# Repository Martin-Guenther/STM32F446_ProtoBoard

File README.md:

# STM32F446_ProtoBoard

A minimalist board with an STM32F446 microcontroller that can be used for prototypes. Most pins of the chip are routed to headers. It is powered over a USB connector and can also act as a USB device. It has SPI flash memory included and must be programmed via SWD.

### License
This is Open-Source-Hardware released under the GNU GPL license.

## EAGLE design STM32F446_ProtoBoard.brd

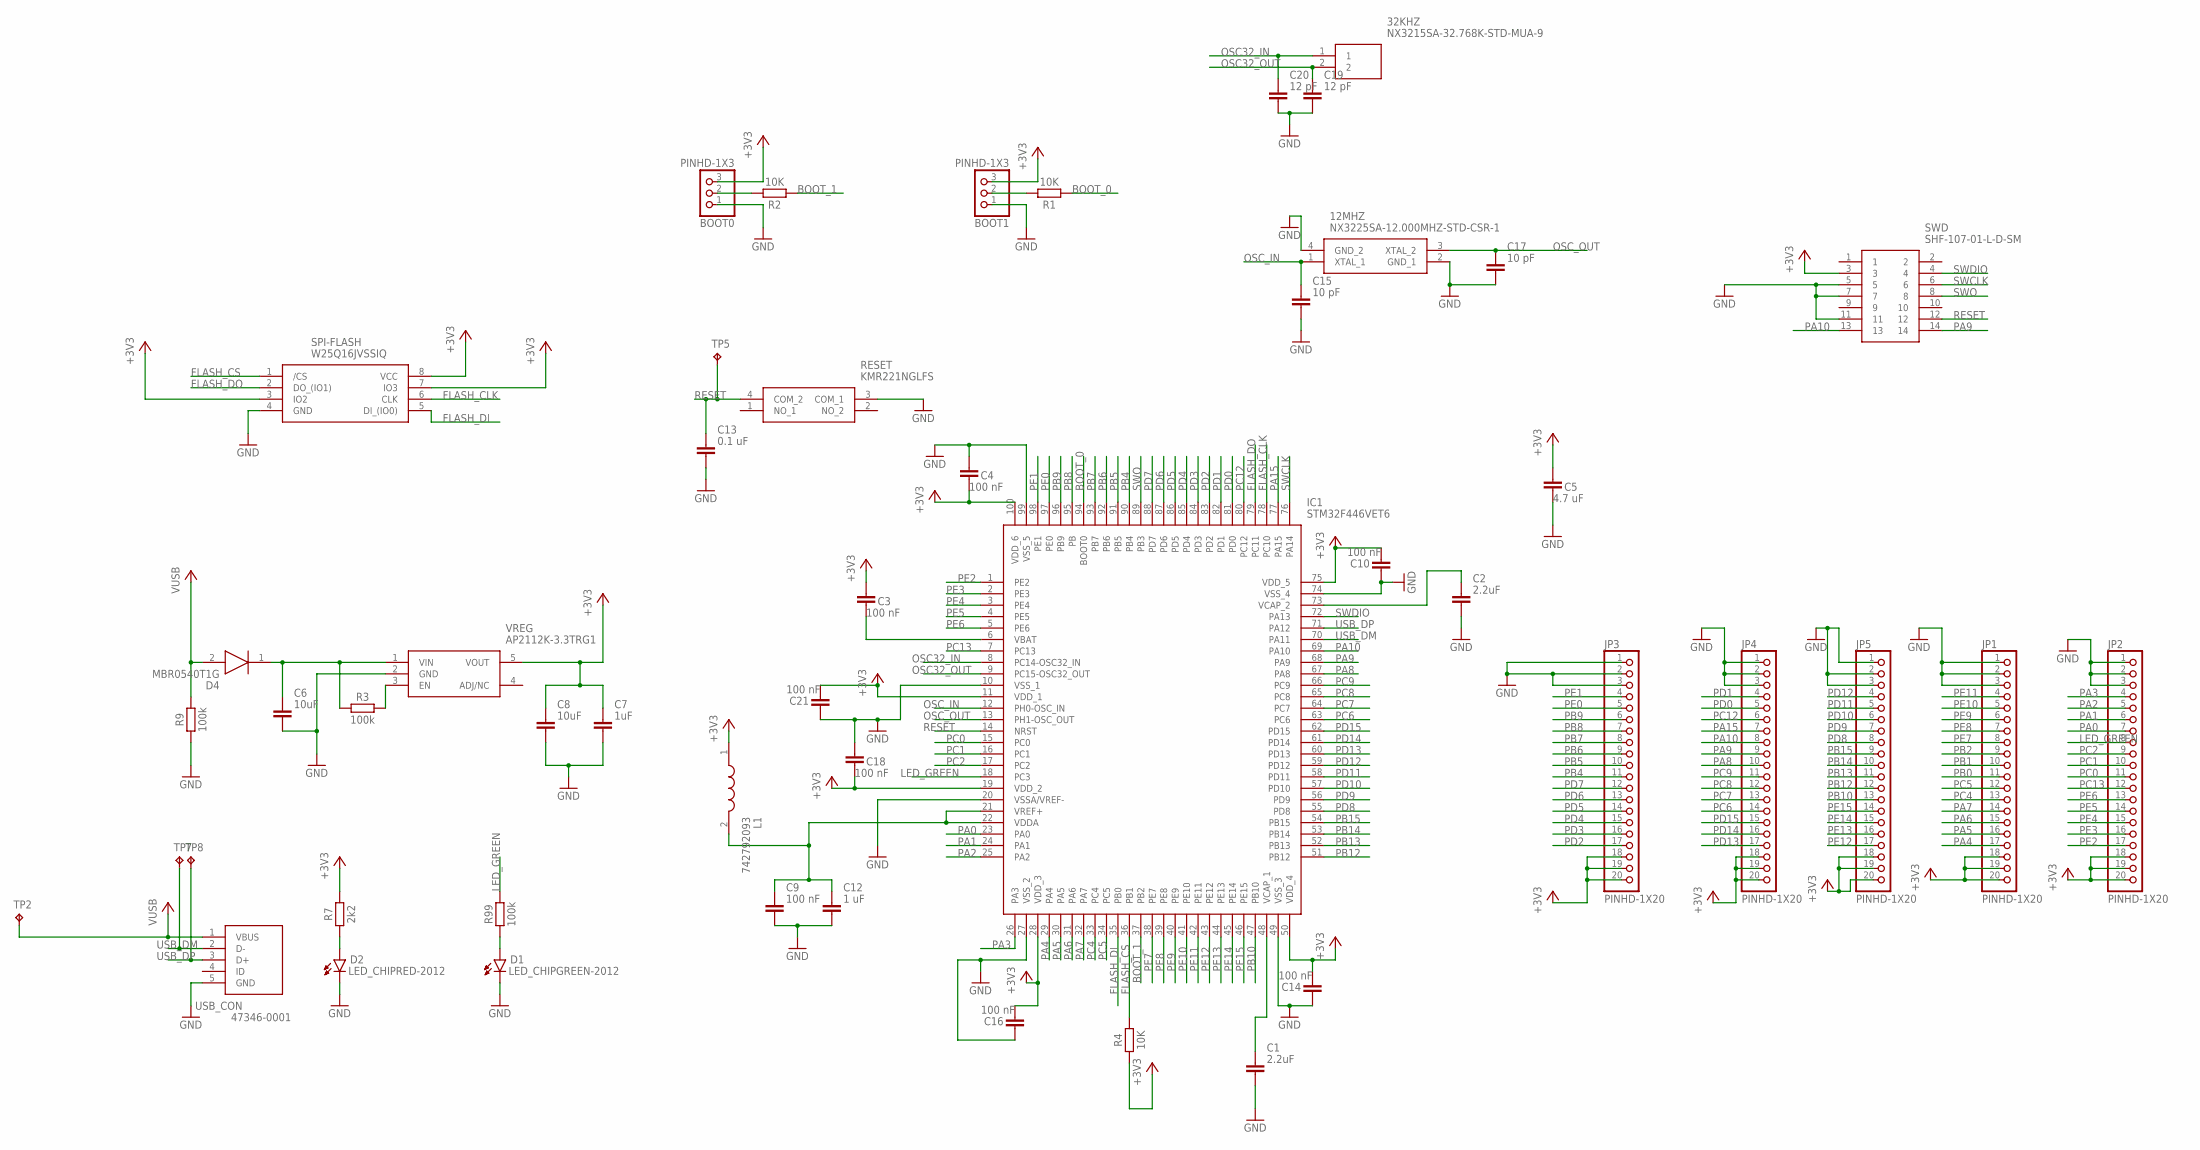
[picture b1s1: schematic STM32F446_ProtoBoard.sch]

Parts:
12MHZ: NX3225SA-12.000MHZ-STD-CSR-1; NX3225SA12000MHZSTDCSR1
32KHZ: NX3215SA-32.768K-STD-MUA-9; NX3215SA
BOOT0, BOOT1: PINHD-1X3; 1X03
C1, C2: 2.2uF; CAPC2012X110
C3, C4, C9, C10, C14, C16, C18, C21: 100 nF; CAPC2012X110
C5: 4.7 uF; CAPC2012X110
C6, C8: 10uF; CAPC2012X110
C7: 1uF; CAPC2012X110
C12: 1 uF; CAPC2012X110
C13: 0.1 uF; CAPC2012X110
C15, C17: 10 pF; CAPC2012X110
C19, C20: 12 pF; CAPC2012X110
D1: LED_CHIPGREEN-2012; LEDC2012X110N_G
D2: LED_CHIPRED-2012; LEDC2012X110N_R
D4: MBR0540T1G; SOD3716X135N
IC1: STM32F446VET6; QFP50P1600X1600X160-100N
JP1, JP2, JP3, JP4, JP5: PINHD-1X20; 1X20
L1: 742792093; CAPC2012X110N
R1, R2, R4: 10K; RESC2012X65
R3, R9, R99: 100k; RESC2012X65
R7: 2k2; RESC2012X65
RESET: KMR221NGLFS
SPI-FLASH: W25Q16JVSSIQ; SOIC127P790X216-8N
SWD: SHF-107-01-L-D-SM; SHF-107-01-X-D-SM
TP2, TP5, TP7, TP8: TPTP20R; TP20R
USB_CON: 47346-0001
VREG: AP2112K-3.3TRG1; SOT95P282X130-5N

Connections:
+3V3: BOOT0.3, BOOT1.3, C3.1, C4.2, C5.1, C7.1, C8.1, C10.2, C14.2, C16.2, C18.2, C21.2, IC1.11 (VDD_1), IC1.19 (VDD_2), IC1.28 (VDD_3), IC1.50 (VDD_4), IC1.75 (VDD_5), IC1.100 (VDD_6), JP1.18, JP1.19, JP1.20, JP2.18, JP2.19, JP2.20, JP3.18, JP3.19, JP3.20, JP4.18, JP4.19, JP4.20, JP5.18, JP5.19, JP5.20, L1.1, R4.1, R7.2, SPI-FLASH.3 (IO2), SPI-FLASH.7 (IO3), SPI-FLASH.8 (VCC), SWD.3, VREG.5 (VOUT)
+5V: D4.2 (A), R9.2, TP2.TP, USB_CON.1 (VBUS)
BOOT_0: IC1.94 (BOOT0), R1.1
BOOT_1: IC1.37 (PB2), R2.1
FLASH_CLK: IC1.78 (PC10), SPI-FLASH.6 (CLK)
FLASH_CS: IC1.36 (PB1), R4.2, SPI-FLASH.1 (/CS)
FLASH_DI: IC1.35 (PB0), SPI-FLASH.5 (DI_(IO0))
FLASH_DO: IC1.79 (PC11), SPI-FLASH.2 (DO_(IO1))
GND: 12MHZ.2 (GND_1), 12MHZ.4 (GND_2), BOOT0.1, BOOT1.1, C1.2, C2.2, C4.1, C5.2, C6.2, C7.2, C8.2, C9.2, C10.1, C12.2, C13.2, C14.1, C15.2, C16.1, C17.2, C18.1, C19.2, C20.2, C21.1, D1.1 (C), D2.1 (C), IC1.10 (VSS_1), IC1.20 (VSSA/VREF-), IC1.27 (VSS_2), IC1.49 (VSS_3), IC1.74 (VSS_4), IC1.99 (VSS_5), JP1.1, JP1.2, JP1.3, JP2.1, JP2.2, JP2.3, JP3.1, JP3.2, JP3.3, JP4.1, JP4.2, JP4.3, JP5.1, JP5.2, JP5.3, R9.1, RESET.3 (COM_1), SPI-FLASH.4 (GND), SWD.5, SWD.7, SWD.11, USB_CON.5 (GND), VREG.2 (GND)
LED_GREEN: IC1.18 (PC3), JP2.8, R99.2
unnamed: C6.1, D4.1 (K), R3.1, VREG.1 (VIN)
unnamed: R3.2, VREG.3 (EN)
unnamed: D2.2 (A), R7.1
unnamed: D1.2 (A), R99.1
unnamed: C1.1, IC1.48 (VCAP_1)
unnamed: C3.2, IC1.6 (VBAT)
unnamed: BOOT1.2, R1.2
unnamed: C2.1, IC1.73 (VCAP_2)
unnamed: BOOT0.2, R2.2
unnamed: C9.1, C12.1, IC1.21 (VREF+), IC1.22 (VDDA), L1.2
OSC32_IN: 32KHZ.1, C20.1, IC1.8 (PC14-OSC32_IN)
OSC32_OUT: 32KHZ.2, C19.1, IC1.9 (PC15-OSC32_OUT)
OSC_IN: 12MHZ.1 (XTAL_1), C15.1, IC1.12 (PH0-OSC_IN)
OSC_OUT: 12MHZ.3 (XTAL_2), C17.1, IC1.13 (PH1-OSC_OUT)
PA0: IC1.23 (PA0), JP2.7
PA1: IC1.24 (PA1), JP2.6
PA2: IC1.25 (PA2), JP2.5
PA3: IC1.26 (PA3), JP2.4
PA4: IC1.29 (PA4), JP1.17
PA5: IC1.30 (PA5), JP1.16
PA6: IC1.31 (PA6), JP1.15
PA7: IC1.32 (PA7), JP1.14
PA8: IC1.67 (PA8), JP4.10
PA9: IC1.68 (PA9), JP4.9, SWD.14
PA10: IC1.69 (PA10), JP4.8, SWD.13
PA15: IC1.77 (PA15), JP4.7
PB0: JP1.11
PB1: JP1.10
PB2: JP1.9
PB4: IC1.90 (PB4), JP3.11
PB5: IC1.91 (PB5), JP3.10
PB6: IC1.92 (PB6), JP3.9
PB7: IC1.93 (PB7), JP3.8
PB8: IC1.95 (PB), JP3.7
PB9: IC1.96 (PB9), JP3.6
PB10: IC1.47 (PB10), JP5.13
PB12: IC1.51 (PB12), JP5.12
PB13: IC1.52 (PB13), JP5.11
PB14: IC1.53 (PB14), JP5.10
PB15: IC1.54 (PB15), JP5.9
PC0: IC1.15 (PC0), JP2.11
PC1: IC1.16 (PC1), JP2.10
PC2: IC1.17 (PC2), JP2.9
PC4: IC1.33 (PC4), JP1.13
PC5: IC1.34 (PC5), JP1.12
PC6: IC1.63 (PC6), JP4.14
PC7: IC1.64 (PC7), JP4.13
PC8: IC1.65 (PC8), JP4.12
PC9: IC1.66 (PC9), JP4.11
PC12: IC1.80 (PC12), JP4.6
PC13: IC1.7 (PC13), JP2.12
PD0: IC1.81 (PD0), JP4.5
PD1: IC1.82 (PD1), JP4.4
PD2: IC1.83 (PD2), JP3.17
PD3: IC1.84 (PD3), JP3.16
PD4: IC1.85 (PD4), JP3.15
PD5: IC1.86 (PD5), JP3.14
PD6: IC1.87 (PD6), JP3.13
PD7: IC1.88 (PD7), JP3.12
PD8: IC1.55 (PD8), JP5.8
PD9: IC1.56 (PD9), JP5.7
PD10: IC1.57 (PD10), JP5.6
PD11: IC1.58 (PD11), JP5.5
PD12: IC1.59 (PD12), JP5.4
PD13: IC1.60 (PD13), JP4.17
PD14: IC1.61 (PD14), JP4.16
PD15: IC1.62 (PD15), JP4.15
PE0: IC1.97 (PE0), JP3.5
PE1: IC1.98 (PE1), JP3.4
PE2: IC1.1 (PE2), JP2.17
PE3: IC1.2 (PE3), JP2.16
PE4: IC1.3 (PE4), JP2.15
PE5: IC1.4 (PE5), JP2.14
PE6: IC1.5 (PE6), JP2.13
PE7: IC1.38 (PE7), JP1.8
PE8: IC1.39 (PE8), JP1.7
PE9: IC1.40 (PE9), JP1.6
PE10: IC1.41 (PE10), JP1.5
PE11: IC1.42 (PE11), JP1.4
PE12: IC1.43 (PE12), JP5.17
PE13: IC1.44 (PE13), JP5.16
PE14: IC1.45 (PE14), JP5.15
PE15: IC1.46 (PE15), JP5.14
RESET: C13.1, IC1.14 (NRST), RESET.4 (COM_2), SWD.12, TP5.TP
SWCLK: IC1.76 (PA14), SWD.6
SWDIO: IC1.72 (PA13), SWD.4
SWO: IC1.89 (PB3), SWD.8
USB_DM: IC1.70 (PA11), TP7.TP, USB_CON.2 (D-)
USB_DP: IC1.71 (PA12), TP8.TP, USB_CON.3 (D+)

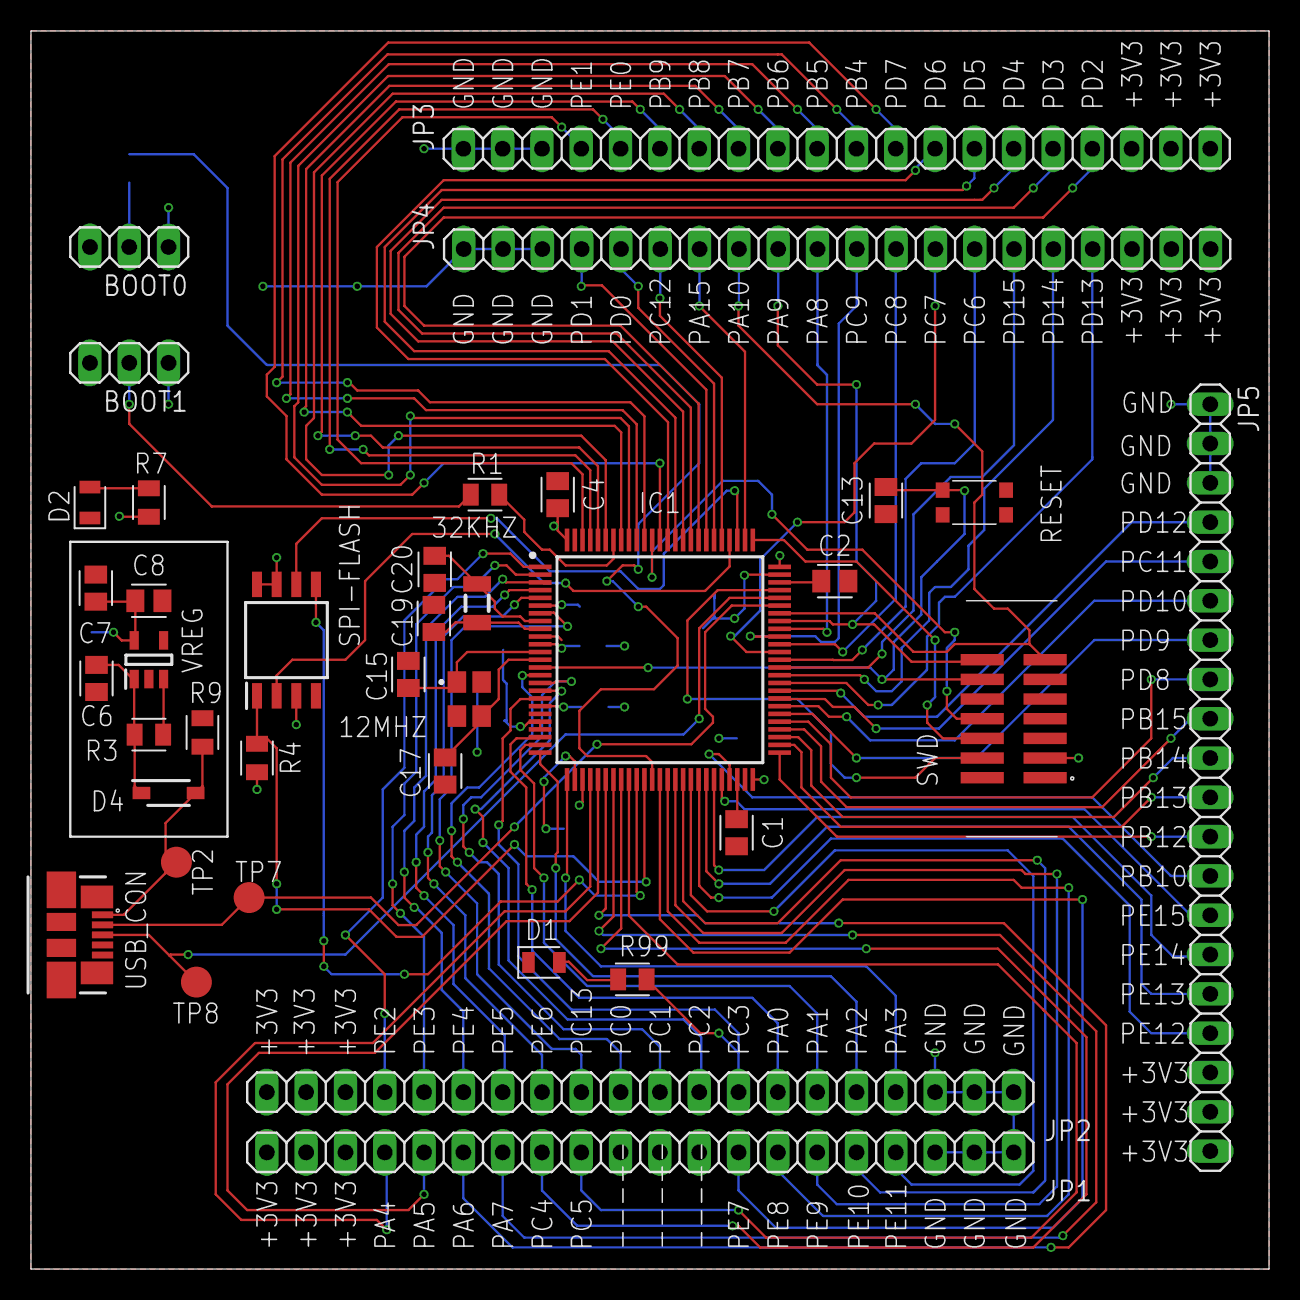
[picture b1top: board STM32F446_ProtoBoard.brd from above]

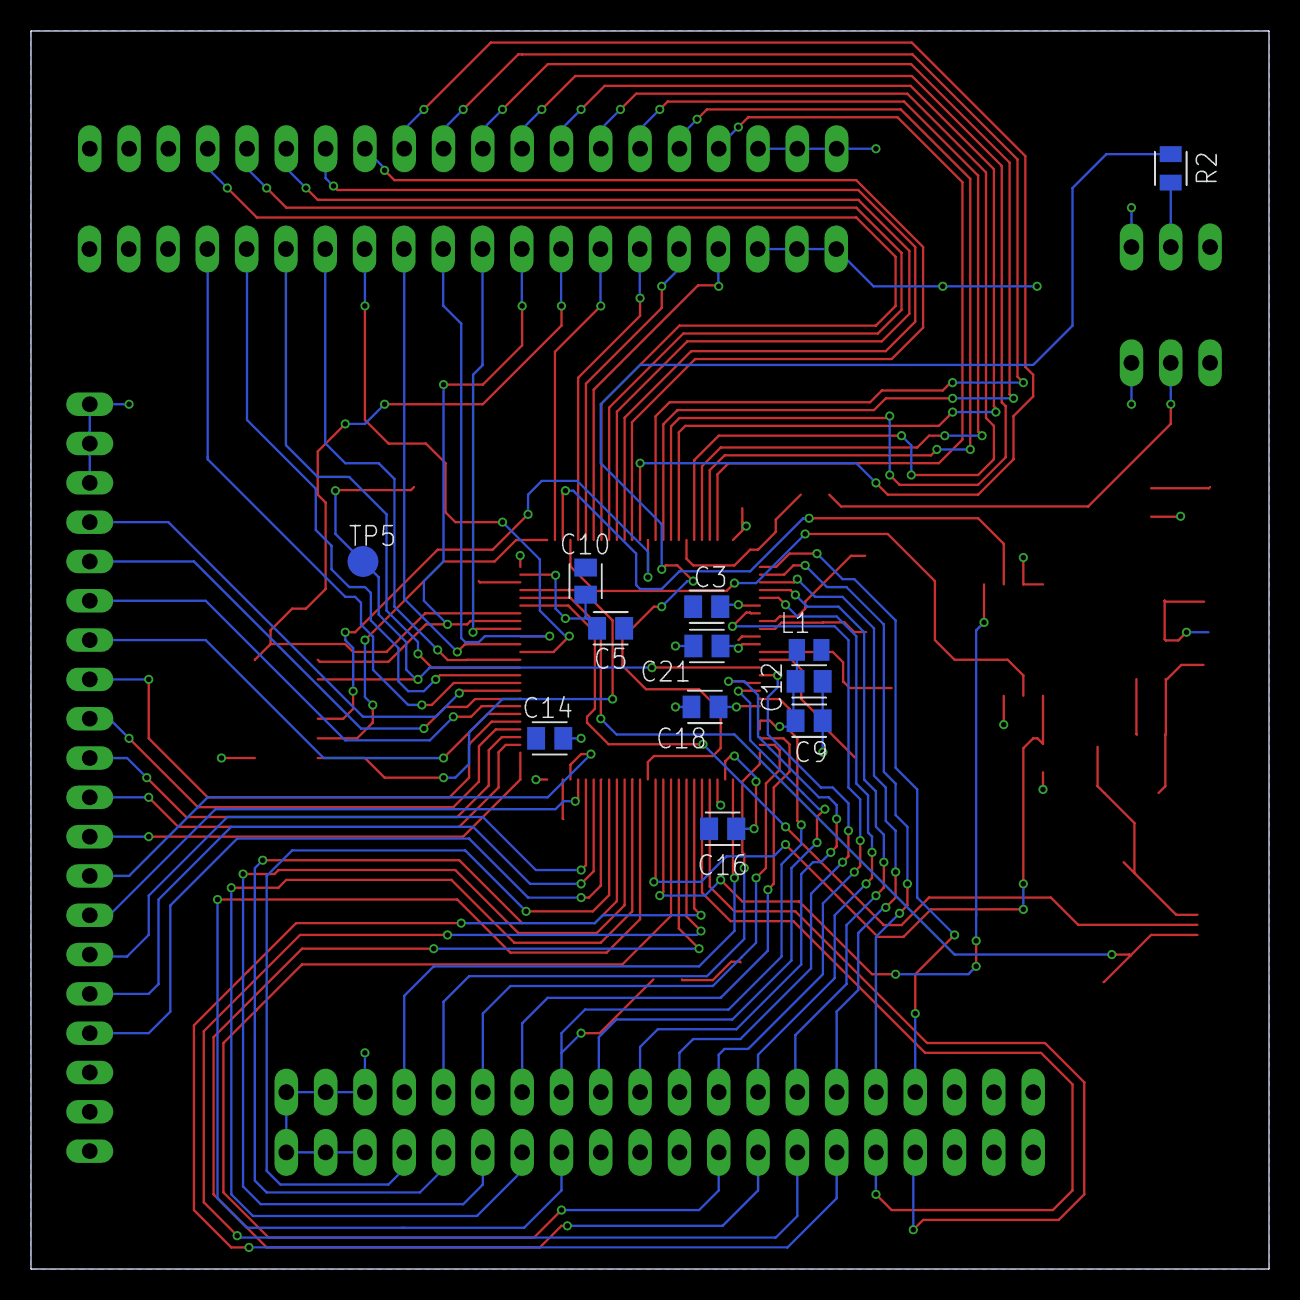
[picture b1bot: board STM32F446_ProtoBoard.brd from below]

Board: 2 copper layers, 80.0 x 80.0 mm, 50 parts (12 on the bottom side), 96 nets.

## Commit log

2020-08-30 Add Eagle files
